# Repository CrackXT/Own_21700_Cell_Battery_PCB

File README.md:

# Own_21700_Cell_Battery_PCB

PCB files for a 21700 cell mount on a separate board

# Description

Compatible with protected 21700 cell type only!

This is an external battery cell board that allows you to mount the appropriate cell holder (21700) and thus have better connection and mounting options in your project or case.

The board can be produced here (AISLER) with the files (.brd and .sch) or by any other PCB manufacturer. -> https://aisler.net/

# Serie

- x

# Layout

Top<br>

Bottom<br>

Routing/Dimensions(inch)<br>

Schematic<br>
Schematic as .pdf at the top of the page.

# License

Open hardware, use it, mod it, whatever you want, feel free...

# Thanks!

Own design and layout.

# Version - Build

v2.0 - 25.06.2022

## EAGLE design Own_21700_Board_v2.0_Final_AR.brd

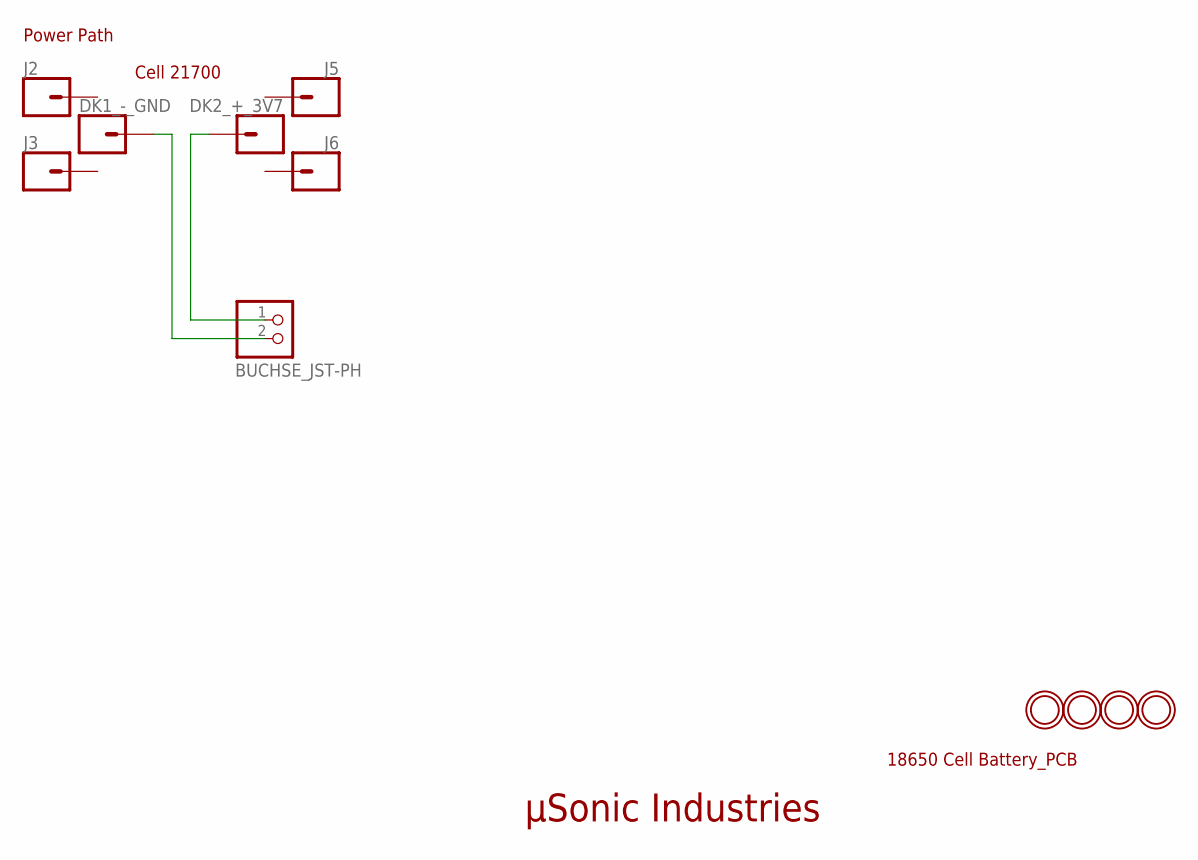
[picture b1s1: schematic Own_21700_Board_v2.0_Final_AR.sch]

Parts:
BUCHSE_JST-PH: JST_2PINOWN; JST-PH-2-THMOWN
DK1_-_GND, DK2_+_3V7: CONN_01PTH_2MM; 1X01_2MM
J2, J3, J5, J6: CONN_01PTH_2MM; 1X01_2MM
U$1, U$2, U$3, U$5: MOUNTINGHOLE2.5; MOUNTINGHOLE_2.5_PLATED

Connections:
3V7: BUCHSE_JST-PH.1 (2), DK2_+_3V7.1
GND: BUCHSE_JST-PH.2 (1), DK1_-_GND.1

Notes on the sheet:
µSonic Industries
18650 Cell Battery_PCB
Power Path
Cell 21700

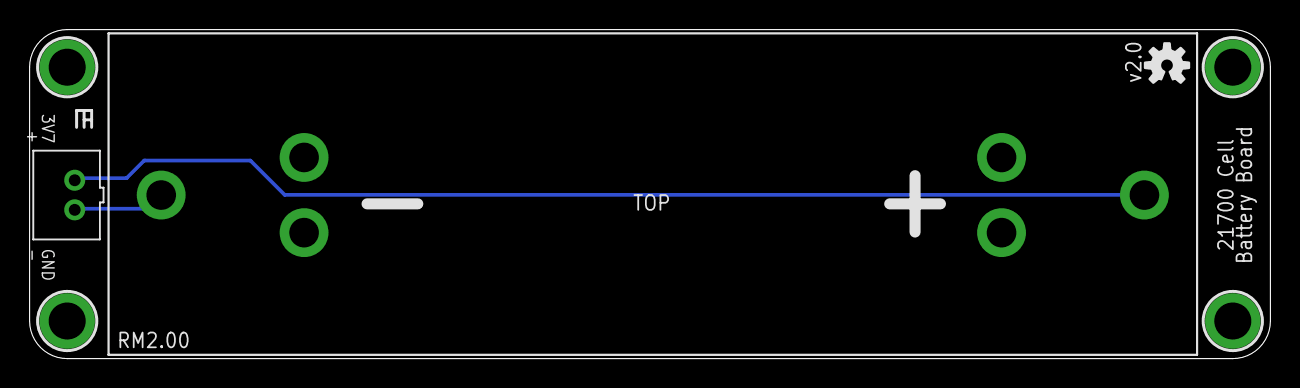
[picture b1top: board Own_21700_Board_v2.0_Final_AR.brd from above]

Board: 2 copper layers, 83.8 x 22.2 mm, 12 parts (0 on the bottom side), 2 nets.

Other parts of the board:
U$4: OSHW-LOGO-S

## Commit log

2022-06-18 Create BOM
2022-06-18 Rename BOM to BOM.md

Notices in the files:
parts and their libraries:
microbuilder: This work is placed in the public domain, and may be freely used for commercial and non-commercial work with the following conditions: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
SparkFun-Aesthetics: Licensing: Creative Commons ShareAlike 4.0 International - https://creativecommons.org/licenses/by-sa/4.0
